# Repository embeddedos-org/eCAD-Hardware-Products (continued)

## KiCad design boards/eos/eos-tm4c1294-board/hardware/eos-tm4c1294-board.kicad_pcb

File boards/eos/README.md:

# EmbeddedOS development boards

Original boards designed by Kartikeydheer Srivastava, all rights reserved (see [Licence](#licence)).
Each board is written as a design file in [tools/eos_boards/boards](../../tools/eos_boards/boards). One command builds the
board's schematic, layout, routing, checks and fabrication outputs; see
[tools/eos_boards/README.md](../../tools/eos_boards/README.md).

| Board | What it is | Layers | ERC | DRC errors | Unconnected | Parity |
|---|---|---|---|---|---|---|
| [EoS Learn RP2350](eos-learn-rp2350) | RP2350A teaching board; Raspberry Pi's own core layout, reproduced to the nanometre | 4 | 0 | 0 | 0 | 0 |
| [EoS Sense Cape](eos-sense-cape) | Sensor cape for PocketBeagle; fit checked pin for pin against PocketBeagle's board file | 2 | 0 | 0 | 0 | 0 |
| [EoS Probe S3](eos-probe-s3) | ESP32-S3 SWD/JTAG + UART debug probe, 1.65–5.5 V targets | 2 | 0 | 0 | 0 | 0 |
| [EoS CM5 Base](eos-cm5-base) | Raspberry Pi CM5 carrier: USB-C power, Gigabit Ethernet, USB 2.0 host, microSD, 40-pin GPIO; connectors checked pad for pad against the CM5 | 4 | 0 | 0 | 0 | 0 |
| [EoS CM4 Base](eos-cm4-base) | Raspberry Pi CM4 carrier: USB-C power, one USB 2.0 port switched between USB-C (device) and USB-A (host), Gigabit Ethernet, microSD, 40-pin GPIO | 4 | 0 | 0 | 0 | 0 |
| [EoS Motion Wing](eos-motion-wing) | FeatherWing: ADXL343 accelerometer and ADT7410 temperature sensor on I2C, address and interrupt jumpers | 2 | 0 | 0 | 0 | 0 |
| [EoS ESP32 DevKit](eos-esp32-devkit) | ESP32-WROOM-32E board: USB-C, CP2102N USB-UART with auto-program, 3.3 V 1 A, DevKitC V4 header grid | 2 | 0 | 0 | 0 | 0 |
| [EoS ATmega328P Board](eos-atmega328p-board) | ATmega328P board that fits Uno R3 shields: USB-C, CH340C USB-UART with Ioff buffers, ICSP header | 2 | 0 | 0 | 0 | 0 |
| [EoS MSP430G2 Board](eos-msp430g2-board) | MSP430G2553 (DIP-20, socketed) board that takes 20-pin BoosterPacks; Spy-Bi-Wire header | 2 | 0 | 0 | 0 | 0 |
| [EoS TM4C123 Board](eos-tm4c123-board) | TM4C123GH6PM board that takes 40-pin BoosterPacks: USB device port, CP2102N USB-UART, SWD | 2 | 0 | 0 | 0 | 0 |
| [EoS KL25 Board](eos-kl25-board) | NXP KL25Z (MKL25Z128VLK4) board that fits Uno R3 shields: USB device port, accelerometer, SWD | 2 | 0 | 0 | 0 | 0 |
| [EoS STM32 64](eos-stm32-64) | STM32F411RE board in the 64-pin Nucleo format: morpho and Uno headers, 7-12 V buck, SWD | 2 | 0 | 0 | 0 | 0 |
| [EoS LPC55S69 Board](eos-lpc55s69-board) | NXP LPC55S69 (dual Cortex-M33) board that fits Uno R3 shields: two USB-C ports, power mux, SWD | 4 | 0 | 0 | 0 | 0 |
| [EoS KE16Z Board](eos-ke16z-board) | NXP KE16Z (MKE16Z64VLF4) board that fits Uno R3 shields: CP2102N USB-UART, CAN pins, SWD | 2 | 0 | 0 | 0 | 0 |
| [EoS RA2E1 Board](eos-ra2e1-board) | Renesas RA2E1 board that fits Uno R3 shields: two Pmod headers, CP2102N on the boot UART, SWD | 2 | 0 | 0 | 0 | 0 |
| [EoS F280049C Board](eos-f280049c-board) | TI TMS320F280049C (C2000) board with two 40-pin BoosterPack sites, four layers: CP2102N USB-UART, JTAG | 4 | 0 | 0 | 0 | 0 |
| [EoS RA4M2 Board](eos-ra4m2-board) | Renesas RA4M2 board that fits Uno R3 shields: SPI and I2C Pmod ports, 40-pin GPIO header, USB device, CP2102N, SWD | 2 | 0 | 0 | 0 | 0 |
| [EoS RL78G13 Board](eos-rl78g13-board) | Renesas RL78/G13 (R5F100LEAFB) stick board: two 30-pin headers 25.4 mm apart, USB-C serial port, TOOL0 debug | 2 | 0 | 0 | 0 | 0 |
| [EoS TM4C1294 Board](eos-tm4c1294-board) | TI TM4C1294NCPDT board with two 40-pin BoosterPack sites, a 98-hole breakout and 10/100 Ethernet, six layers: USB device port, CP2102N USB-UART, SWD/JTAG | 6 | 0 | 0 | 0 | 0 |
| [EoS Feather RP2040](eos-feather-rp2040) | RP2040 board in the Feather form factor: USB-C, LiPo charger, 16 MB QSPI flash, STEMMA QT, SWD | 4 | 0 | 0 | 0 | 0 |
| [EoS EPU Board](eos-epu-up5k) | iCE40UP5K FPGA board for EPU, EmbeddedOS's RISC-V SoC: USB-C with FT2232H (iceprog flash programming and UART), 16 MB flash, two Pmod ports, JTAG header | 4 | 0 | 0 | 0 | 0 |

Each board folder contains:

- the KiCad project;
- Gerbers and drill files;
- BOM and pick-and-place files;
- a STEP model;
- the schematic as a PDF;
- renders;
- `build-report.json`, which records the check counts.

The KiCad projects open in KiCad 10 or later; the boards are saved in KiCad 10's format.
The Gerbers, drill files, BOM, STEP and PDF need no KiCad at all.

None of these boards has been manufactured or tested on the bench. Each README says what was
checked and what was not.

## Licence

These boards are **not open source**, and they are **not** under the MIT licence that
covers this repository's own code. They are Copyright (c) 2026 Kartikeydheer Srivastava, all
rights reserved. Each board's `LICENSE.txt` has the full terms. In short:

- **Anyone** may view them, download or clone this repository, open the files to look at them
  and run its tests. Copying or changing the designs, making boards from them or selling them
  needs Kartikeydheer Srivastava's written permission, which may be given for a fee. To ask,
  write to kartikeydheer@gmail.com.
- **EmbeddedOS (EoS) Research Foundation** may, free of charge, publish them and its own
  changed versions for viewing, change them for its own projects, and make and lend boards for
  its own development, research, teaching and demonstrations. It may not sell boards or pass
  the designs on. Kartikeydheer Srivastava can withdraw this permission with 30 days' notice
  by email or letter.
- **Third-party material** keeps its own licence: Raspberry Pi's RP2350A core layout (MIT) on
  EoS Learn RP2350, and footprints, symbols and 3D models from KiCad's libraries. Each board's
  `LICENSE.txt` lists what it uses.

What the licence covers:

- every board folder here, except the generic libraries copied into a board's
  `hardware/symbols/` and `hardware/footprints/EoS_Packages.pretty`, which are MIT like the
  generator that writes them;
- in `tools/eos_boards`: the boards' design files `boards/eos_*.py`, `boards/owner.py`, the
  licence terms `boards/licence_terms.txt`, and the footprint library drawn for the module
  carriers, `footprints/EoS_Connectors.pretty`.

The rest of `tools/eos_boards` (the generator, the reference extractors, `symbols/` and
`footprints/generate.py` with the `EoS_Packages.pretty` it writes) and its tests stay under the
repository's MIT licence.

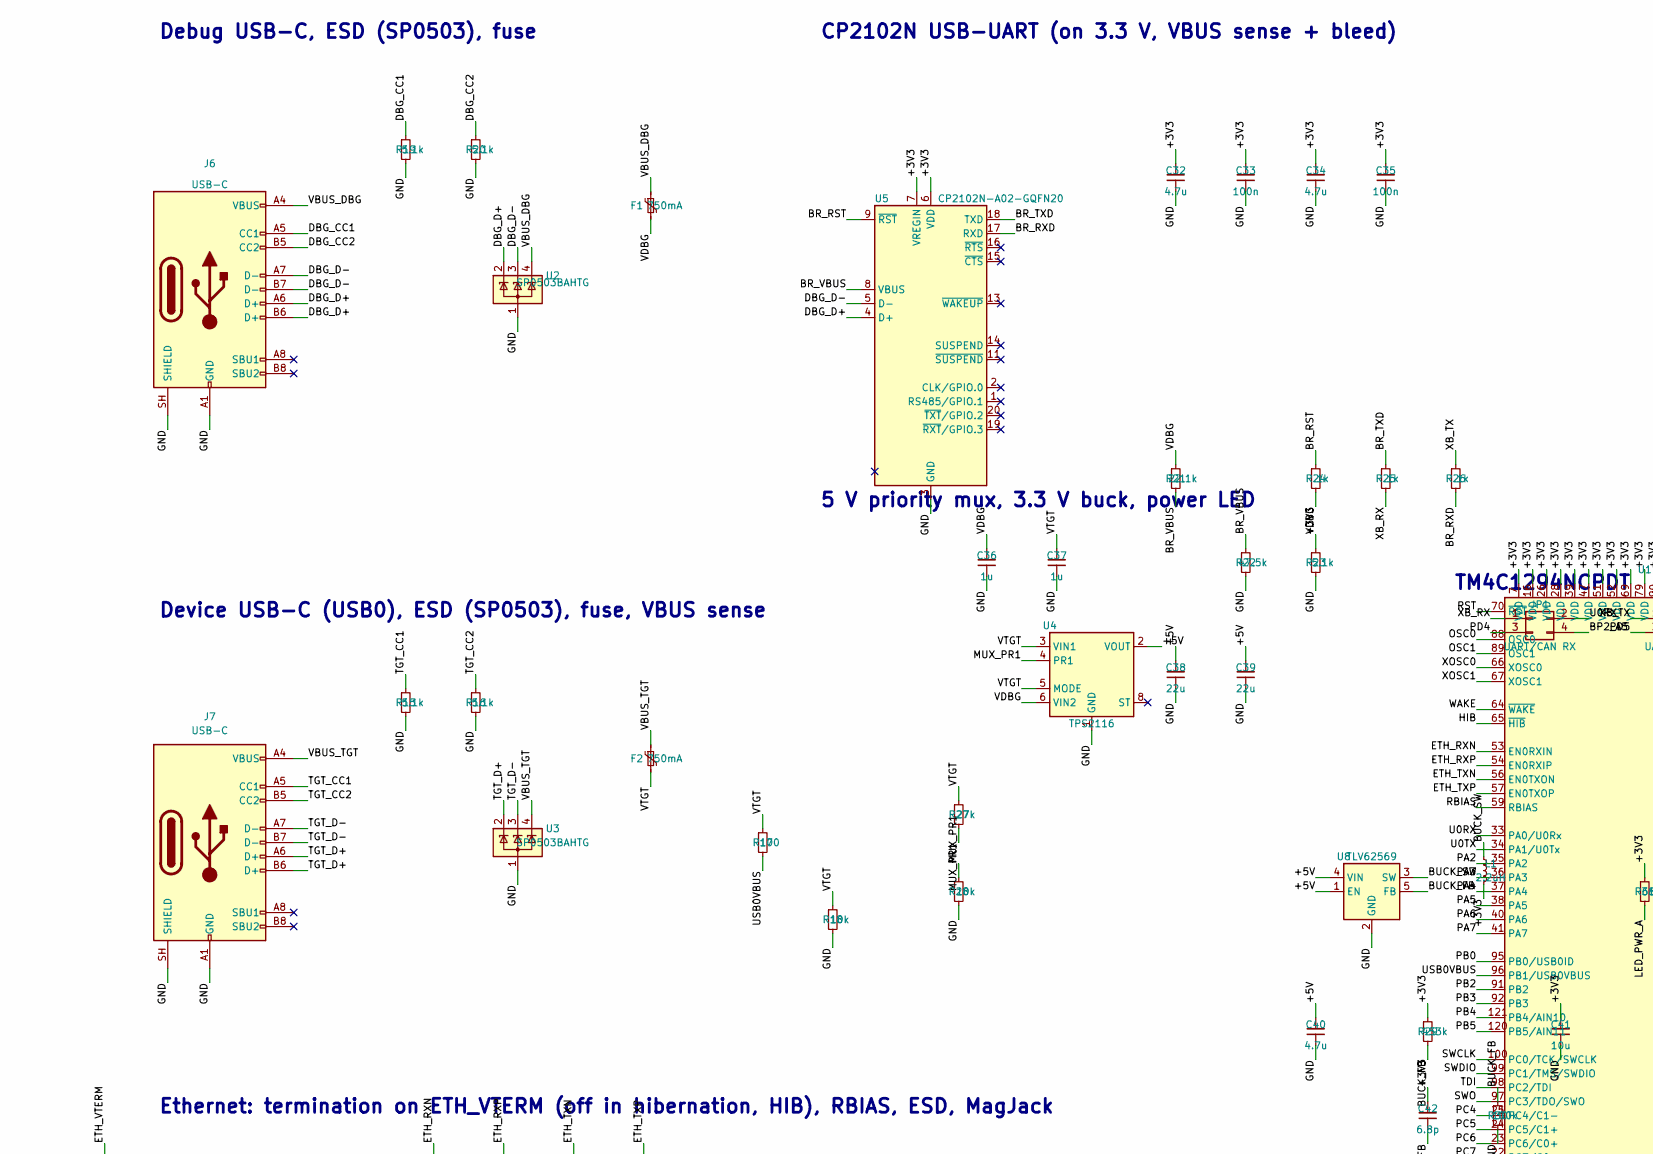
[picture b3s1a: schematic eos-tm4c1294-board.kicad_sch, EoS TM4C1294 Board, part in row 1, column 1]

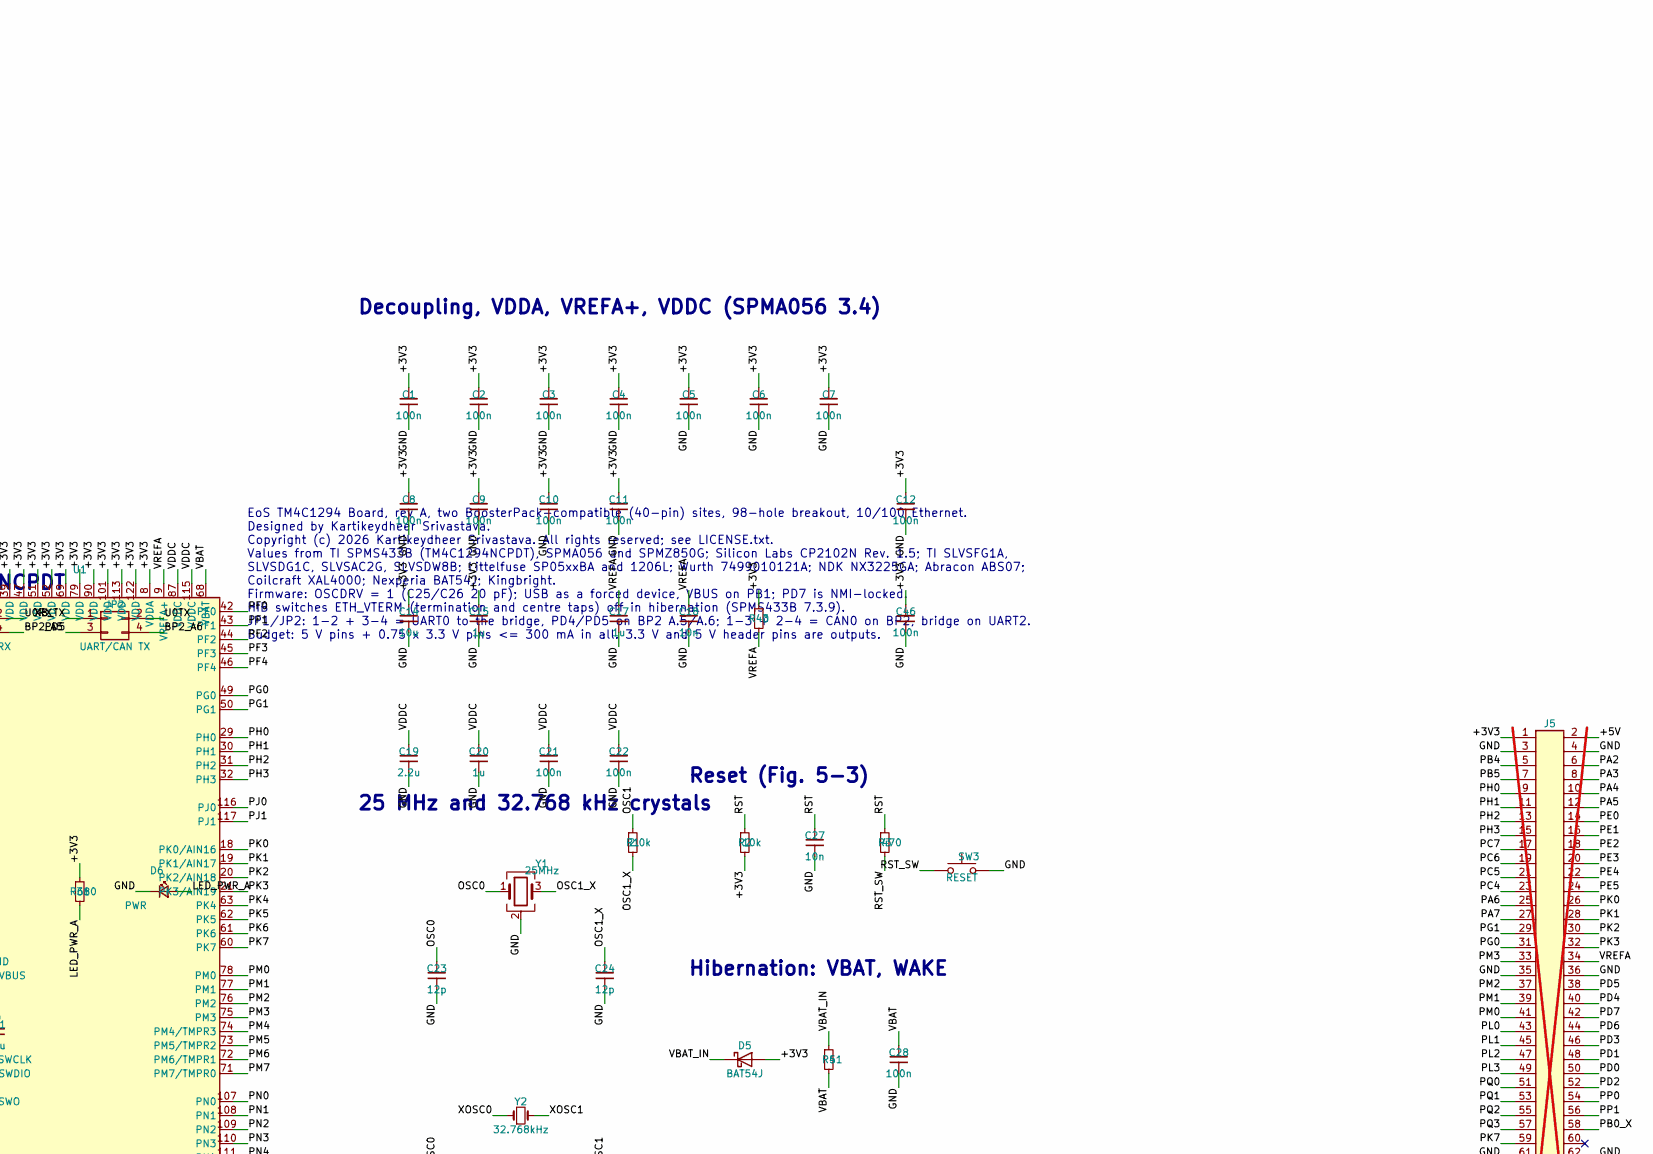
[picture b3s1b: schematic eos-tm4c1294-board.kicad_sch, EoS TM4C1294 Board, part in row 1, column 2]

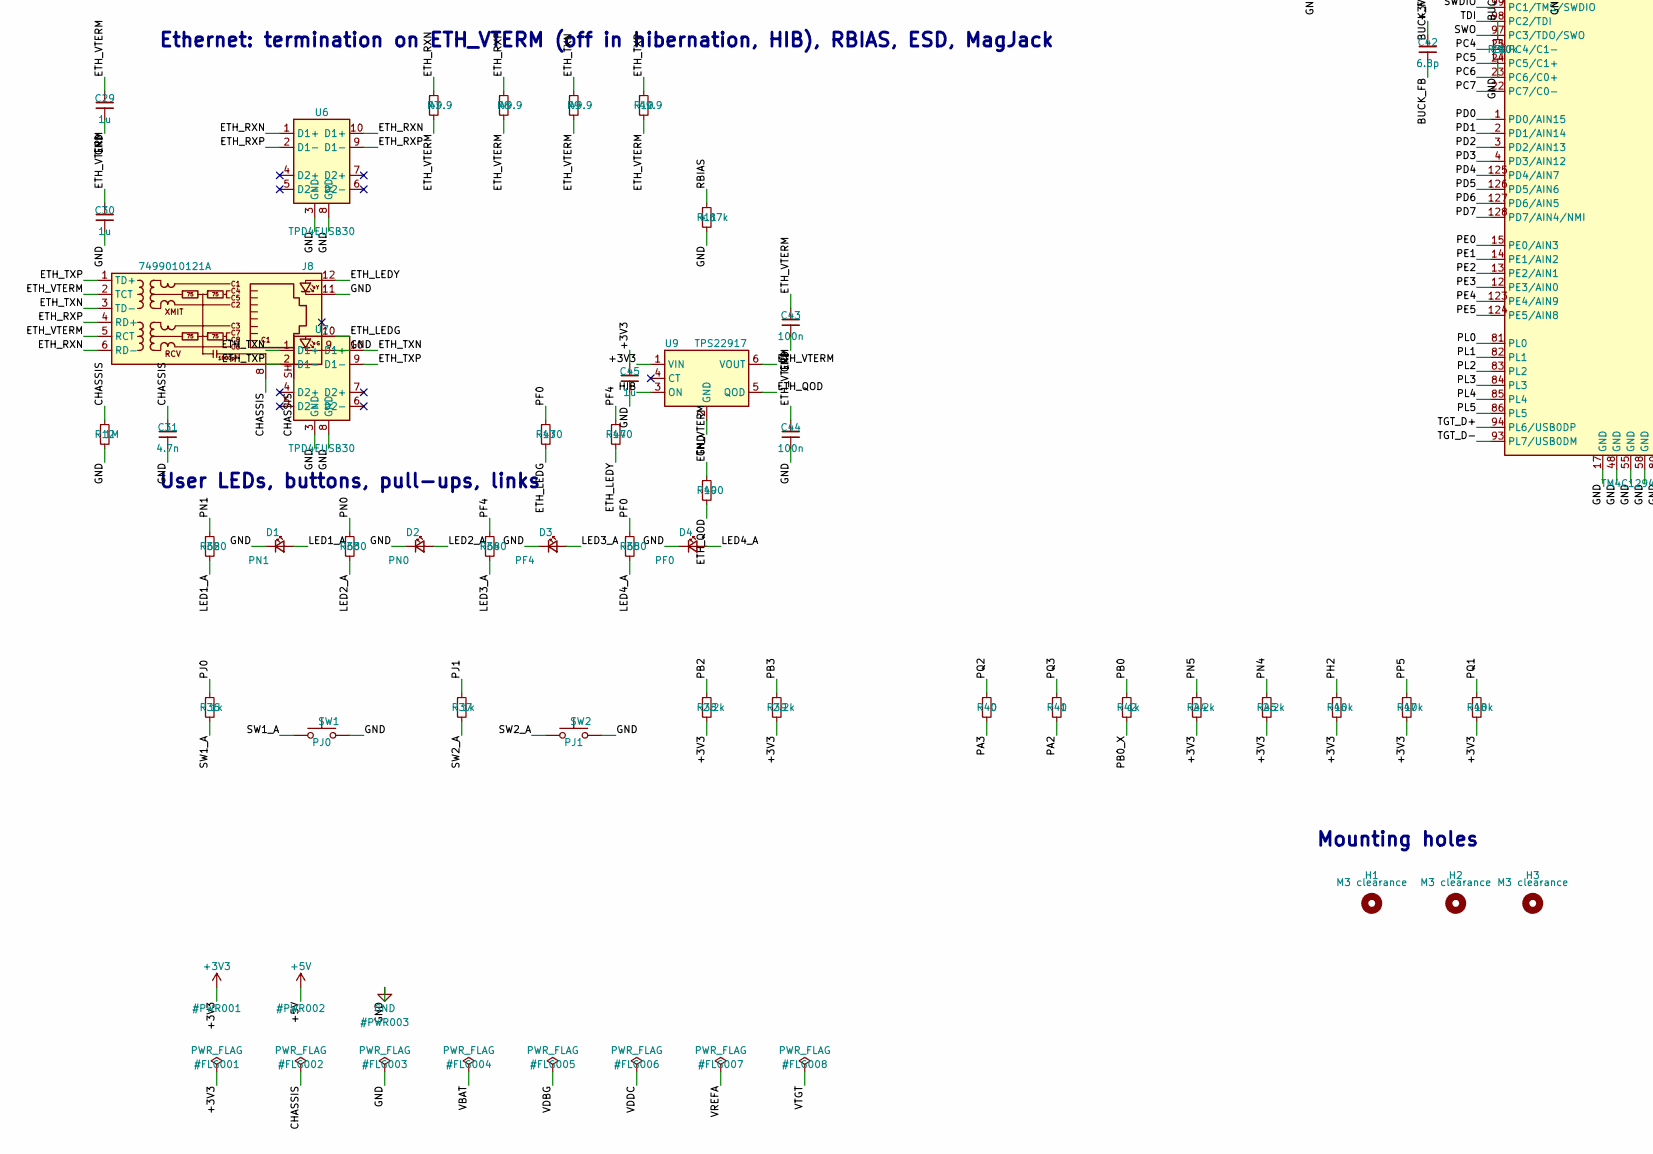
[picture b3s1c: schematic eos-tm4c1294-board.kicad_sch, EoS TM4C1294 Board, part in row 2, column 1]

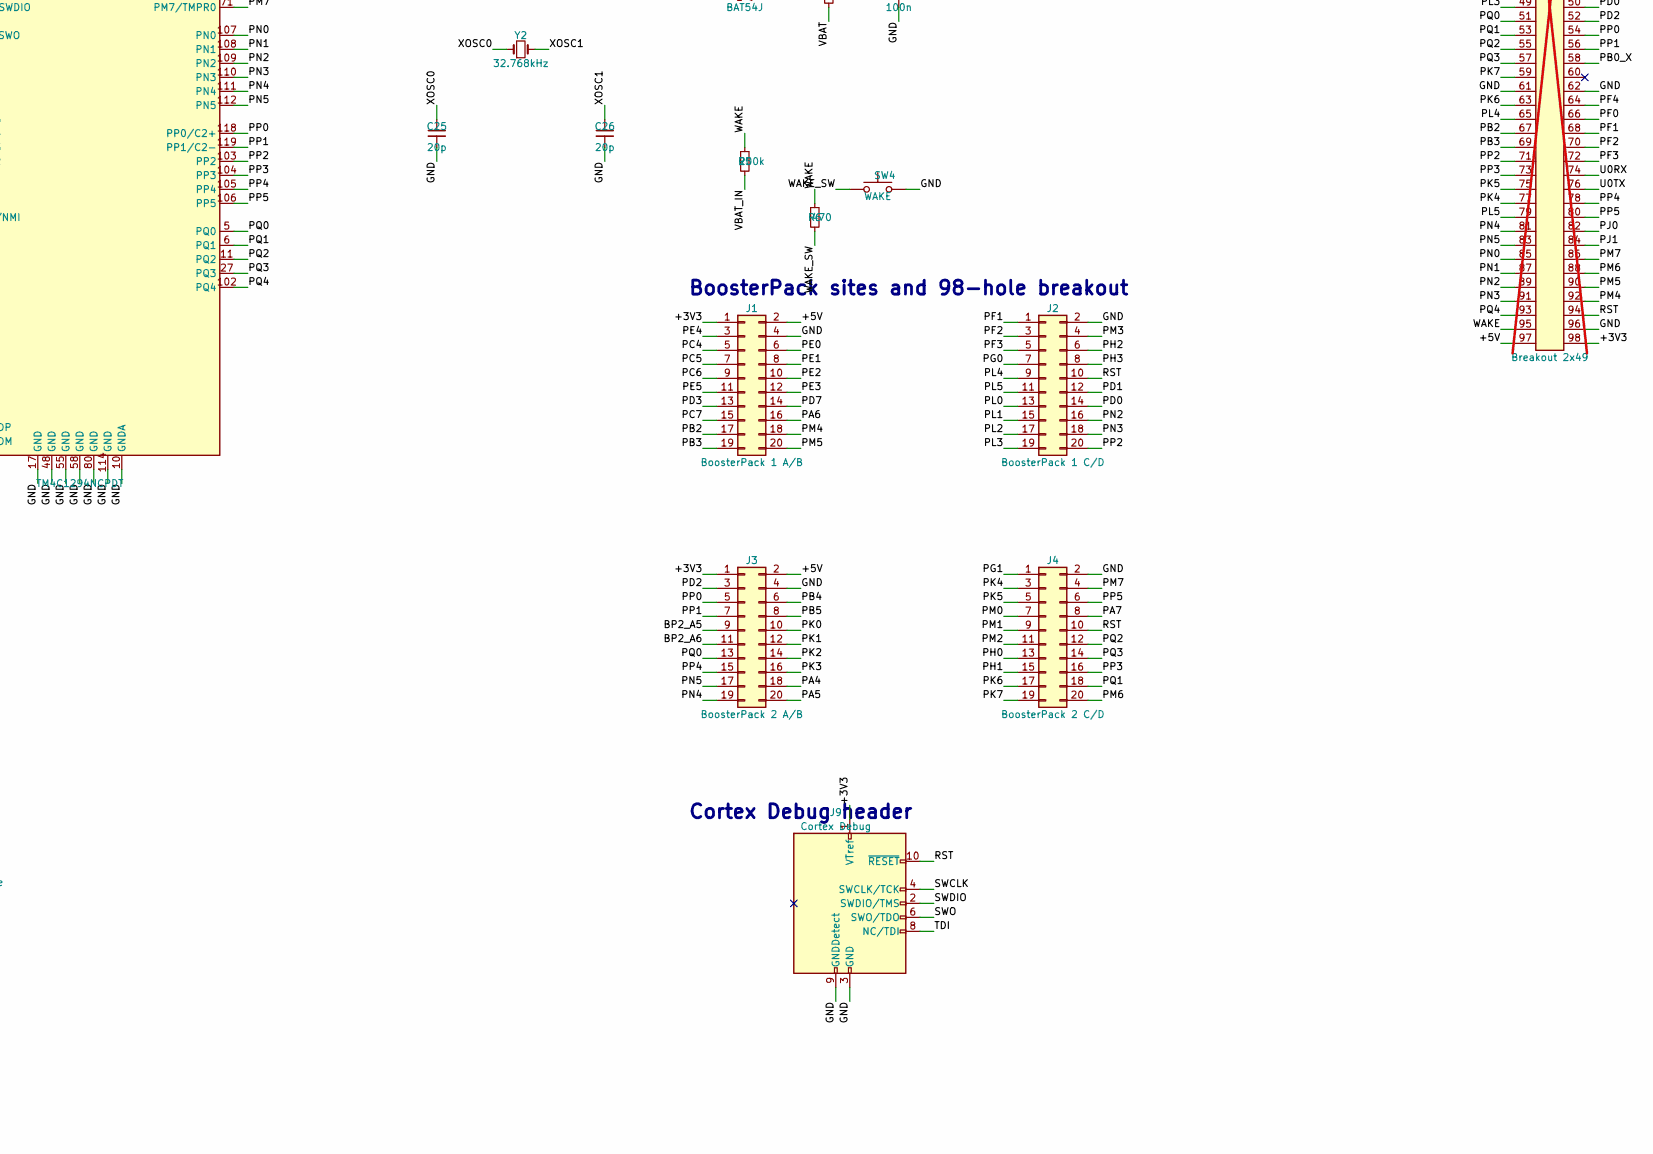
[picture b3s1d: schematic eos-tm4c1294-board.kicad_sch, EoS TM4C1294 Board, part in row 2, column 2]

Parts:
C1, C2, C3, C4, C5, C6, C7, C8, C9, C10, C11, C12, C21, C22, C28, C33, C35, C43, C44, C46: 100n; C_0402_1005Metric; MPN GRM155R71C104KA88D
C14: 10u; C_0805_2012Metric; MPN GRM21BR61C106KE15L
C15, C17, C20, C29, C30, C36, C37, C45: 1u; C_0603_1608Metric; MPN GCM188R71C105KA64D
C18, C27: 10n; C_0402_1005Metric; MPN GRM155R71H103KA88D
C19: 2.2u; C_0603_1608Metric; MPN GRM188R71A225KE15D
C23, C24: 12p; C_0402_1005Metric; MPN GRM1555C1H120JA01D
C25, C26: 20p; C_0402_1005Metric; MPN GCM1555C1H200JA16D
C31: 4.7n; C_1812_4532Metric; MPN C1812C472KGRACTU
C32, C34: 4.7u; C_0603_1608Metric; MPN GRM188R61C475KE11D
C38, C39: 22u; C_1206_3216Metric; MPN GRM31CR71A226KE15L
C40: 4.7u; C_0805_2012Metric; MPN GRM21BR71A475KE51L
C41: 10u; C_0805_2012Metric; MPN GRM21BR71A106KA73L
C42: 6.8p; C_0402_1005Metric; MPN GRM1555C1H6R8CA01D
D1: PN1; LED_0603_1608Metric; MPN APTD1608LCGCK
D2: PN0; LED_0603_1608Metric; MPN APTD1608LCGCK
D3: PF4; LED_0603_1608Metric; MPN APTD1608LCGCK
D4: PF0; LED_0603_1608Metric; MPN APTD1608LCGCK
D5: BAT54J; D_SOD-323F; MPN BAT54J
D6: PWR; LED_0603_1608Metric; MPN APTD1608LCGCK
F1, F2: 750mA; Fuse_1206_3216Metric; MPN 1206L075THYR
H1, H2, H3: M3 clearance; MountingHole_3.2mm_M3
J1: BoosterPack 1 A/B; PinHeader_2x10_P2.54mm_Vertical; MPN SSW-110-23-F-D
J2: BoosterPack 1 C/D; PinHeader_2x10_P2.54mm_Vertical; MPN SSW-110-23-F-D
J3: BoosterPack 2 A/B; PinHeader_2x10_P2.54mm_Vertical; MPN SSW-110-23-F-D
J4: BoosterPack 2 C/D; PinHeader_2x10_P2.54mm_Vertical; MPN SSW-110-23-F-D
J5: Breakout 2x49; PinHeader_2x49_P2.54mm_Vertical; not fitted
J6, J7: USB-C; USB_C_Receptacle_HRO_TYPE-C-31-M-12; MPN TYPE-C-31-M-12
J8: 7499010121A; RJ45_Wuerth_7499010121A_Horizontal; MPN 7499010121A
J9: Cortex Debug; PinHeader_2x05_P1.27mm_Vertical_SMD; MPN FTSH-105-01-L-DV-K
JP1: UART/CAN RX; PinHeader_2x02_P2.54mm_Vertical; MPN TSW-102-07-G-D
JP2: UART/CAN TX; PinHeader_2x02_P2.54mm_Vertical; MPN TSW-102-07-G-D
L1: 2.2uH; L_Coilcraft_XAL4020-XXX; MPN XAL4020-222MEC
R1: 2.0k; R_0402_1005Metric
R2, R18, R28, R46, R47, R48: 10k; R_0402_1005Metric
R3, R6, R13, R14: 470; R_0402_1005Metric
R4: 51; R_0402_1005Metric
R5: 200k; R_0402_1005Metric
R7, R8, R9, R10: 49.9; R_0402_1005Metric
R11: 4.87k; R_0402_1005Metric
R12: 1M; R_1206_3216Metric
R15, R16, R19, R20, R23: 5.1k; R_0402_1005Metric
R17, R49: 100; R_0402_1005Metric
R21: 22.1k; R_0402_1005Metric
R22: 47.5k; R_0402_1005Metric
R24, R25, R26, R36, R37, R42: 1k; R_0402_1005Metric
R27: 27k; R_0402_1005Metric
R29: 453k; R_0402_1005Metric
R30: 100k; R_0402_1005Metric
R31, R32, R33, R34, R35: 680; R_0402_1005Metric
R38, R39, R44, R45: 2.2k; R_0402_1005Metric
R40, R41, R43: 0; R_0402_1005Metric
SW1: PJ0; SW_Push_1P1T_NO_CK_KMR2; MPN KMR221G LFS
SW2: PJ1; SW_Push_1P1T_NO_CK_KMR2; MPN KMR221G LFS
SW3: RESET; SW_Push_1P1T_NO_CK_KMR2; MPN KMR221G LFS
SW4: WAKE; SW_Push_1P1T_NO_CK_KMR2; MPN KMR221G LFS
U1: TM4C1294NCPDT; TQFP-128_14x14mm_P0.4mm; MPN TM4C1294NCPDTI3
U2, U3: SP0503BAHTG; SOT-143; MPN SP0503BAHTG
U4: TPS2116; SOT-583-8; MPN TPS2116DRLR
U5: CP2102N-A02-GQFN20; SiliconLabs_QFN-20-1EP_3x3mm_P0.5mm_EP1.8x1.8mm; MPN CP2102N-A02-GQFN20R
U6, U7: TPD4EUSB30; USON-10_2.5x1.0mm_P0.5mm; MPN TPD4EUSB30DQAR
U8: TLV62569; SOT-23-5; MPN TLV62569DBVR
U9: TPS22917; SOT-23-6; MPN TPS22917DBVR
Y1: 25MHz; Crystal_SMD_3225-4Pin_3.2x2.5mm; MPN NX3225GA-25.000M-STD-CRG-2
Y2: 32.768kHz; Crystal_SMD_3215-2Pin_3.2x1.5mm; MPN ABS07-32.768KHZ-T

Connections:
+3V3: C1.1, C2.1, C3.1, C4.1, C5.1, C6.1, C7.1, C8.1, C9.1, C10.1, C11.1, C12.1, C14.1, C15.1, C32.1, C33.1, C34.1, C35.1, C41.1, C42.1, C45.1, C46.1, D5.2 (A), J1.1, J3.1, J5.1, J5.98, J9.1 (VTref), L1.2, R2.2, R24.2, R29.1, R31.1, R38.2, R39.2, R43.1, R44.2, R45.2, R46.2, R47.2, R48.2, U1.7 (VDD), U1.8 (VDDA), U1.16 (VDD), U1.26 (VDD), U1.28 (VDD), U1.39 (VDD), U1.47 (VDD), U1.51 (VDD), U1.52 (VDD), U1.69 (VDD), U1.79 (VDD), U1.90 (VDD), U1.101 (VDD), U1.113 (VDD), U1.122 (VDD), U5.6 (VDD), U5.7 (VREGIN), U9.1 (VIN)
+5V: C38.1, C39.1, C40.1, J1.2, J3.2, J5.2, J5.97, U4.2 (VOUT), U4.7 (VOUT), U8.1 (EN), U8.4 (VIN)
/BP2_A5: J3.9, JP1.4
/BP2_A6: J3.11, JP2.4
/BR_RST: R24.1, U5.9 (~RST)
/BR_RXD: R26.2, U5.17 (RXD)
/BR_TXD: R25.1, U5.18 (TXD)
/BR_VBUS: R21.2, R22.1, U5.8 (VBUS)
/BUCK_FB: C42.2, R29.2, R30.1, U8.5 (FB)
/BUCK_SW: L1.1, U8.3 (SW)
/CHASSIS: C31.1, J8.8, J8.SH, R12.1
/DBG_CC1: J6.A5 (CC1), R19.1
/DBG_CC2: J6.B5 (CC2), R20.1
/DBG_D+: J6.A6 (D+), J6.B6 (D+), U2.2 (K), U5.4 (D+)
/DBG_D-: J6.A7 (D-), J6.B7 (D-), U2.3 (K), U5.5 (D-)
/ETH_LEDG: J8.10, R13.2
/ETH_LEDY: J8.12, R14.2
/ETH_QOD: R49.2, U9.5 (QOD)
/ETH_RXN: J8.6 (RD-), R7.1, U1.53 (EN0RXIN), U6.1 (D1+), U6.10 (D1+)
/ETH_RXP: J8.4 (RD+), R8.1, U1.54 (EN0RXIP), U6.2 (D1-), U6.9 (D1-)
/ETH_TXN: J8.3 (TD-), R9.1, U1.56 (EN0TXON), U7.1 (D1+), U7.10 (D1+)
/ETH_TXP: J8.1 (TD+), R10.1, U1.57 (EN0TXOP), U7.2 (D1-), U7.9 (D1-)
/ETH_VTERM: C29.1, C30.1, C43.1, C44.1, J8.2 (TCT), J8.5 (RCT), R7.2, R8.2, R9.2, R10.2, R49.1, U9.6 (VOUT)
/HIB: U1.65 (~HIB), U9.3 (ON)
/LED1_A: D1.2 (A), R32.2
/LED2_A: D2.2 (A), R33.2
/LED3_A: D3.2 (A), R34.2
/LED4_A: D4.2 (A), R35.2
/LED_PWR_A: D6.2 (A), R31.2
/MUX_PR1: R27.2, R28.1, U4.4 (PR1)
/OSC0: C23.1, U1.88 (OSC0), Y1.1
/OSC1: R1.1, U1.89 (OSC1)
/OSC1_X: C24.1, R1.2, Y1.3
/PA2: J5.6, R41.2, U1.35 (PA2)
/PA3: J5.8, R40.2, U1.36 (PA3)
/PA4: J3.18, J5.10, U1.37 (PA4)
/PA5: J3.20, J5.12, U1.38 (PA5)
/PA6: J1.16, J5.25, U1.40 (PA6)
/PA7: J4.8, J5.27, U1.41 (PA7)
/PB0: R42.1, U1.95 (PB0/USB0ID)
/PB0_X: J5.58, R42.2
/PB2: J1.17, J5.67, R38.1, U1.91 (PB2)
/PB3: J1.19, J5.69, R39.1, U1.92 (PB3)
/PB4: J3.6, J5.5, U1.121 (PB4/AIN10)
/PB5: J3.8, J5.7, U1.120 (PB5/AIN11)
/PC4: J1.5, J5.23, U1.25 (PC4/C1-)
/PC5: J1.7, J5.21, U1.24 (PC5/C1+)
/PC6: J1.9, J5.19, U1.23 (PC6/C0+)
/PC7: J1.15, J5.17, U1.22 (PC7/C0-)
/PD0: J2.14, J5.50, U1.1 (PD0/AIN15)
/PD1: J2.12, J5.48, U1.2 (PD1/AIN14)
/PD2: J3.3, J5.52, U1.3 (PD2/AIN13)
/PD3: J1.13, J5.46, U1.4 (PD3/AIN12)
/PD4: J5.40, JP1.3, U1.125 (PD4/AIN7)
/PD5: J5.38, JP2.3, U1.126 (PD5/AIN6)
/PD6: J5.44, U1.127 (PD6/AIN5)
/PD7: J1.14, J5.42, U1.128 (PD7/AIN4/NMI)
/PE0: J1.6, J5.14, U1.15 (PE0/AIN3)
/PE1: J1.8, J5.16, U1.14 (PE1/AIN2)
/PE2: J1.10, J5.18, U1.13 (PE2/AIN1)
/PE3: J1.12, J5.20, U1.12 (PE3/AIN0)
/PE4: J1.3, J5.22, U1.123 (PE4/AIN9)
/PE5: J1.11, J5.24, U1.124 (PE5/AIN8)
/PF0: J5.66, R13.1, R35.1, U1.42 (PF0)
/PF1: J2.1, J5.68, U1.43 (PF1)
/PF2: J2.3, J5.70, U1.44 (PF2)
/PF3: J2.5, J5.72, U1.45 (PF3)
/PF4: J5.64, R14.1, R34.1, U1.46 (PF4)
/PG0: J2.7, J5.31, U1.49 (PG0)
/PG1: J4.1, J5.29, U1.50 (PG1)
/PH0: J4.13, J5.9, U1.29 (PH0)
/PH1: J4.15, J5.11, U1.30 (PH1)
/PH2: J2.6, J5.13, R46.1, U1.31 (PH2)
/PH3: J2.8, J5.15, U1.32 (PH3)
/PJ0: J5.82, R36.1, U1.116 (PJ0)
/PJ1: J5.84, R37.1, U1.117 (PJ1)
/PK0: J3.10, J5.26, U1.18 (PK0/AIN16)
/PK1: J3.12, J5.28, U1.19 (PK1/AIN17)
/PK2: J3.14, J5.30, U1.20 (PK2/AIN18)
/PK3: J3.16, J5.32, U1.21 (PK3/AIN19)
/PK4: J4.3, J5.77, U1.63 (PK4)
/PK5: J4.5, J5.75, U1.62 (PK5)
/PK6: J4.17, J5.63, U1.61 (PK6)
/PK7: J4.19, J5.59, U1.60 (PK7)
/PL0: J2.13, J5.43, U1.81 (PL0)
/PL1: J2.15, J5.45, U1.82 (PL1)
/PL2: J2.17, J5.47, U1.83 (PL2)
/PL3: J2.19, J5.49, U1.84 (PL3)
/PL4: J2.9, J5.65, U1.85 (PL4)
/PL5: J2.11, J5.79, U1.86 (PL5)
/PM0: J4.7, J5.41, U1.78 (PM0)
/PM1: J4.9, J5.39, U1.77 (PM1)
/PM2: J4.11, J5.37, U1.76 (PM2)
/PM3: J2.4, J5.33, U1.75 (PM3)
/PM4: J1.18, J5.92, U1.74 (PM4/TMPR3)
/PM5: J1.20, J5.90, U1.73 (PM5/TMPR2)
/PM6: J4.20, J5.88, U1.72 (PM6/TMPR1)
/PM7: J4.4, J5.86, U1.71 (PM7/TMPR0)
/PN0: J5.85, R33.1, U1.107 (PN0)
/PN1: J5.87, R32.1, U1.108 (PN1)
/PN2: J2.16, J5.89, U1.109 (PN2)
/PN3: J2.18, J5.91, U1.110 (PN3)
/PN4: J3.19, J5.81, R45.1, U1.111 (PN4)
/PN5: J3.17, J5.83, R44.1, U1.112 (PN5)
/PP0: J3.5, J5.54, U1.118 (PP0/C2+)
/PP1: J3.7, J5.56, U1.119 (PP1/C2-)
/PP2: J2.20, J5.71, U1.103 (PP2)
/PP3: J4.16, J5.73, U1.104 (PP3)
/PP4: J3.15, J5.78, U1.105 (PP4)
/PP5: J4.6, J5.80, R47.1, U1.106 (PP5)
/PQ0: J3.13, J5.51, U1.5 (PQ0)
/PQ1: J4.18, J5.53, R48.1, U1.6 (PQ1)
/PQ2: J4.12, J5.55, R40.1, U1.11 (PQ2)
/PQ3: J4.14, J5.57, R41.1, U1.27 (PQ3)
/PQ4: J5.93, U1.102 (PQ4)
/RBIAS: R11.1, U1.59 (RBIAS)
/RST: C27.1, J2.10, J4.10, J5.94, J9.10 (~RESET), R2.1, R3.1, U1.70 (~RST)
/RST_SW: R3.2, SW3.1
/SW1_A: R36.2, SW1.1
/SW2_A: R37.2, SW2.1
/SWCLK: J9.4 (SWCLK/TCK), U1.100 (PC0/TCK/SWCLK)
/SWDIO: J9.2 (SWDIO/TMS), U1.99 (PC1/TMS/SWDIO)
/SWO: J9.6 (SWO/TDO), U1.97 (PC3/TDO/SWO)
/TDI: J9.8 (NC/TDI), U1.98 (PC2/TDI)
/TGT_CC1: J7.A5 (CC1), R15.1
/TGT_CC2: J7.B5 (CC2), R16.1
/TGT_D+: J7.A6 (D+), J7.B6 (D+), U1.94 (PL6/USB0DP), U3.2 (K)
/TGT_D-: J7.A7 (D-), J7.B7 (D-), U1.93 (PL7/USB0DM), U3.3 (K)
/U0RX: J5.74, JP1.2, U1.33 (PA0/U0Rx)
/U0TX: J5.76, JP2.2, U1.34 (PA1/U0Tx)
/USB0VBUS: R17.2, U1.96 (PB1/USB0VBUS)
/VBAT: C28.1, R4.2, U1.68 (VBAT)
/VBAT_IN: D5.1 (K), R4.1, R5.2
/VBUS_DBG: F1.1, J6.A4 (VBUS), J6.A9 (VBUS), J6.B4 (VBUS), J6.B9 (VBUS), U2.4 (K)
/VBUS_TGT: F2.1, J7.A4 (VBUS), J7.A9 (VBUS), J7.B4 (VBUS), J7.B9 (VBUS), U3.4 (K)
/VDBG: C36.1, F1.2, R21.1, R23.1, U4.6 (VIN2)
/VDDC: C19.1, C20.1, C21.1, C22.1, U1.87 (VDDC), U1.115 (VDDC)
/VREFA: C17.1, C18.1, J5.34, R43.2, U1.9 (VREFA+)
/VTGT: C37.1, F2.2, R17.1, R18.1, R27.1, U4.3 (VIN1), U4.5 (MODE)
/WAKE: J5.95, R5.1, R6.1, U1.64 (~WAKE)
/WAKE_SW: R6.2, SW4.1
/XB_RX: JP1.1, R25.2
/XB_TX: JP2.1, R26.1
/XOSC0: C25.1, U1.66 (XOSC0), Y2.1
/XOSC1: C26.1, U1.67 (XOSC1), Y2.2
GND: C1.2, C2.2, C3.2, C4.2, C5.2, C6.2, C7.2, C8.2, C9.2, C10.2, C11.2, C12.2, C14.2, C15.2, C17.2, C18.2, C19.2, C20.2, C21.2, C22.2, C23.2, C24.2, C25.2, C26.2, C27.2, C28.2, C29.2, C30.2, C31.2, C32.2, C33.2, C34.2, C35.2, C36.2, C37.2, C38.2, C39.2, C40.2, C41.2, C43.2, C44.2, C45.2, C46.2, D1.1 (K), D2.1 (K), D3.1 (K), D4.1 (K), D6.1 (K), J1.4, J2.2, J3.4, J4.2, J5.3, J5.4, J5.35, J5.36, J5.61, J5.62, J5.96, J6.A1 (GND), J6.A12 (GND), J6.B1 (GND), J6.B12 (GND), J6.SH (SHIELD), J7.A1 (GND), J7.A12 (GND), J7.B1 (GND), J7.B12 (GND), J7.SH (SHIELD), J8.9, J8.11, J9.3 (GND), J9.5 (GND), J9.9 (GNDDetect), R11.2, R12.2, R15.2, R16.2, R18.2, R19.2, R20.2, R22.2, R23.2, R28.2, R30.2, SW1.2, SW2.2, SW3.2, SW4.2, U1.10 (GNDA), U1.17 (GND), U1.48 (GND), U1.55 (GND), U1.58 (GND), U1.80 (GND), U1.114 (GND), U2.1 (A), U3.1 (A), U4.1 (GND), U5.3 (GND), U5.12 (GND), U5.21 (GND), U6.3 (GND), U6.8 (GND), U7.3 (GND), U7.8 (GND), U8.2 (GND), U9.2 (GND), Y1.2 (G), Y1.4 (G)

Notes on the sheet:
Debug USB-C, ESD (SP0503), fuse
CP2102N USB-UART (on 3.3 V, VBUS sense + bleed)
Device USB-C (USB0), ESD (SP0503), fuse, VBUS sense
5 V priority mux, 3.3 V buck, power LED
TM4C1294NCPDT
Decoupling, VDDA, VREFA+, VDDC (SPMA056 3.4)
25 MHz and 32.768 kHz crystals
Reset (Fig. 5-3)
Hibernation: VBAT, WAKE
Ethernet: termination on ETH_VTERM (off in hibernation, HIB), RBIAS, ESD, MagJack
BoosterPack sites and 98-hole breakout
Cortex Debug header
User LEDs, buttons, pull-ups, links
Mounting holes
EoS TM4C1294 Board, rev A, two BoosterPack-compatible (40-pin) sites, 98-hole breakout, 10/100 Ethernet. Designed by Kartikeydheer Srivastava. Copyright (c) 2026 Kartikeydheer Srivastava. All rights reserved; see LICENSE.txt. Values from TI SPMS433B (TM4C1294NCPDT), SPMA056 and SPMZ850G; Silicon La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

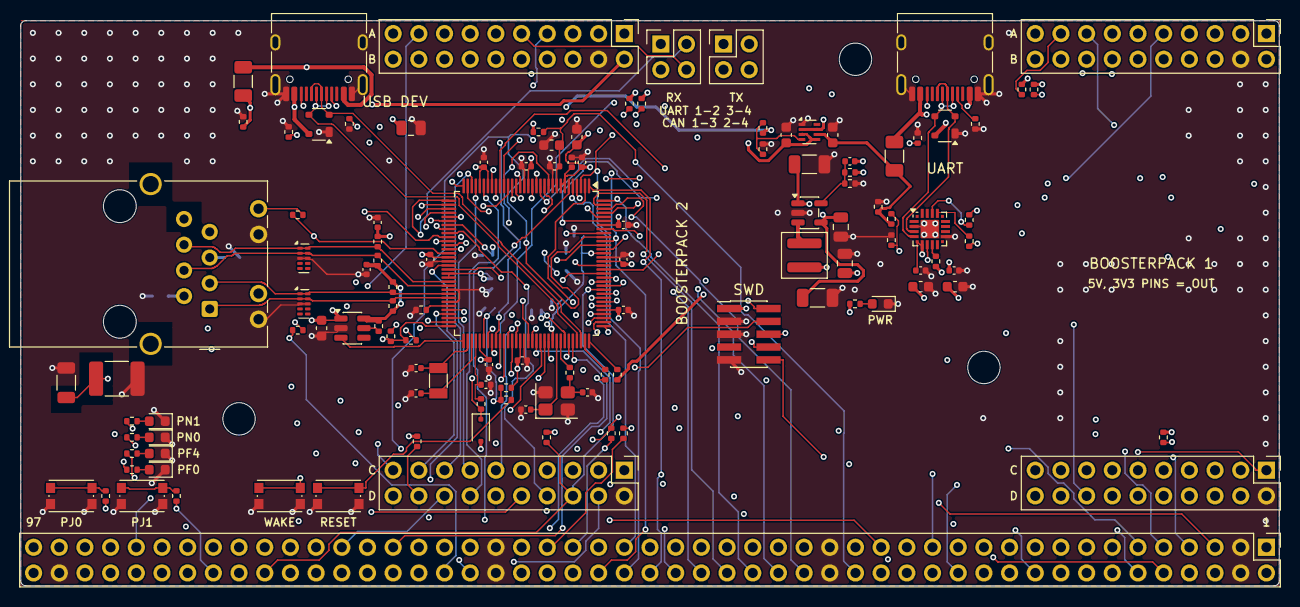
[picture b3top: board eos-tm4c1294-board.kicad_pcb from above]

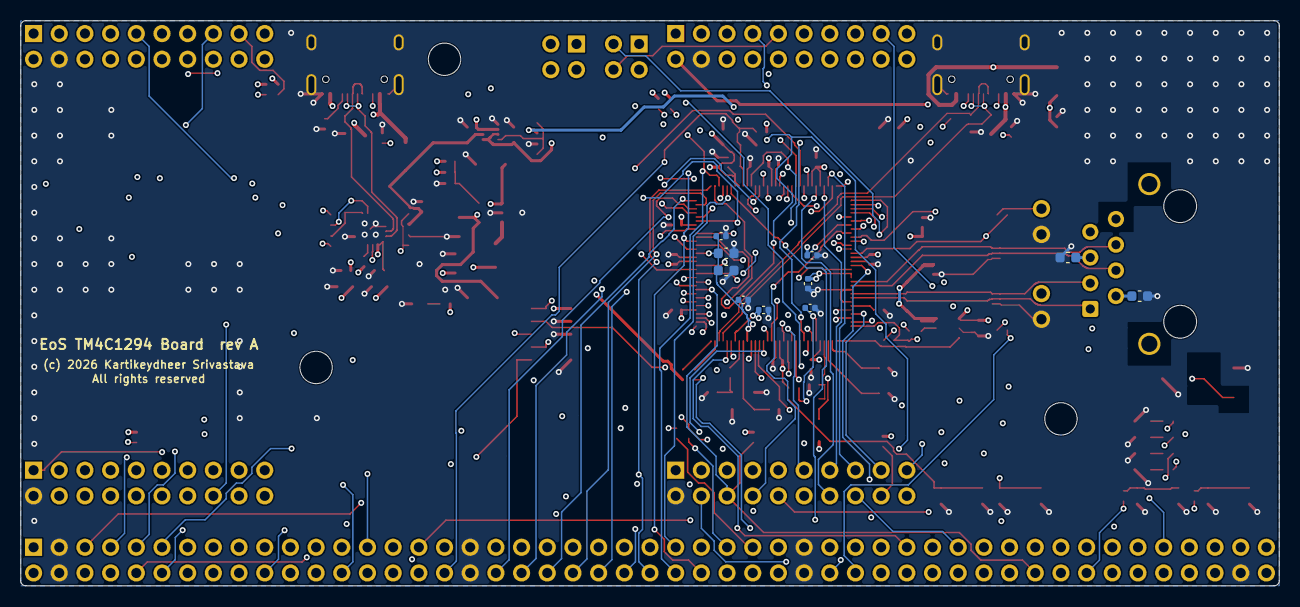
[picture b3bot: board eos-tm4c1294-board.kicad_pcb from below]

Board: 6 copper layers, 124.5 x 55.9 mm, 131 parts (10 on the bottom side), 146 nets.

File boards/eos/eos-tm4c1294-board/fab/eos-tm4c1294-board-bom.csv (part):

"Refs","Value","Footprint","Manufacturer","MPN","Description","Qty","DNP"
"C1-C12,C21,C22,C28,C33,C35,C43,C44,C46","100n","Capacitor_SMD:C_0402_1005Metric","Murata","GRM155R71C104KA88D","Capacitor 100 nF X7R 16 V 0402, CBAT at VBAT pin 68: 5.1 us with RBAT, under 0.7 V/us (TI SPMS433B Figure 7-2, Table 27-29; errata ELEC#02),Capacitor 100 nF X7R 16 V 0402, CP2102N VDD, at the pin (Silicon Labs CP2102N data sheet Rev. 1.5 Figure 2.3),Capacitor 100 nF X7R 16 V 0402, CP2102N VREGIN, at the pin (Silicon Labs CP2102N data sheet Rev. 1.5 Figure 2.3),Capacitor 100 nF X7R 16 V 0402, VDD pin 101, joined to the pin before routing (TI SPMA056 3.4.3),Capacitor 100 nF X7R 16 V 0402, VDD pin 113, joined to the pin before routing (TI SPMA056 3.4.3),Capacitor 100 nF X7R 16 V 0402, VDD pin 122, joined to the pin before routing (TI SPMA056 3.4.3),Capacitor 100 nF X7R 16 V 0402, VDD pin 16, joined to the pin before routing (TI SPMA056 3.4.3),Capacitor 100 nF X7R 16 V 0402, VDD pin 26/28, joined to the pin before routing (TI SPMA056 3.4.3),Capacitor 100 nF X7R 16 V 0402, VDD pin 39, joined to the pin before routing (TI SPMA056 3.4.3; on the bottom side under the chip, reached through a via inside the pad ring (Table 7)),Capacitor 100 nF X7R 16 V 0402, VDD pin 47, joined to the pin before routing (TI SPMA056 3.4.3),Capacitor 100 nF X7R 16 V 0402, VDD pin 51/52, joined to the pin before routing (TI SPMA056 3.4.3; on the bottom side under the chip, through a via inside the pad ring (Table 7); its ground pad also takes GND pins 55 and 58),Capacitor 100 nF X7R 16 V 0402, VDD pin 69, joined to the pin before routing (TI SPMA056 3.4.3),Capacitor 100 nF X7R 16 V 0402, VDD pin 7, joined to the pin before routing (TI SPMA056 3.4.3),Capacitor 100 nF X7R 16 V 0402, VDD pin 79/80, joined to the pin before routing (TI SPMA056 3.4.3),Capacitor 100 nF X7R 16 V 0402, VDD pin 90, on the bottom side under the chip (TI SPMA056 3.4.3; Table 7 puts most of the 128-pin package's capacitors on the back),Capacitor 100 nF X7R 16 V 0402, VDDA pin 8 (TI SPMA056 3.4.3),Capacitor 100 nF X7R 16 V 0402, receive-pair termination supply (TI SPMS433B Figure 20-13: 0.1 uF at each pair's resistors),Capacitor 100 nF X7R 16 V 0402, transmit-pair termination supply (TI SPMS433B Figure 20-13),Capacitor 100 nF X7R 16 V 10% 0402, VDDC at pin 115, on the bottom side after C19 (TI SPMA056 3.4.2),Capacitor 100 nF X7R 16 V 10% 0402, VDDC at pin 87, on the bottom side under the chip next to pin 87's via (TI SPMA056 3.4.2, Table 6)","20",""
"C14","10u","Capacitor_SMD:C_0805_2012Metric","Murata","GRM21BR61C106KE15L","Capacitor 10 uF X5R 16 V 0805, VDD/VDDA bulk: 2-22 uF (TI SPMA056 3.4.3)","1",""
"C15,C17,C20,C29,C30,C36,C37,C45","1u","Capacitor_SMD:C_0603_1608Metric","Murata","GCM188R71C105KA64D","Capacitor 1 uF X7R 16 V 0603, CREF at VREFA+ pin 9 to GNDA (TI SPMA056 3.4.5),Capacitor 1 uF X7R 16 V 0603, TPS2116 VIN1, on its pin's side (TI SLVSFG1A section 9),Capacitor 1 uF X7R 16 V 0603, TPS2116 VIN2, on its pin's side (TI SLVSFG1A section 9),Capacitor 1 uF X7R 16 V 0603, TPS22917 input (TI SLVSDW8B section 11: CIN 1 uF),Capacitor 1 uF X7R 16 V 0603, VDDA pin 8 (TI SPMA056 3.4.4),Capacitor 1 uF X7R 16 V 0603, receive centre tap J8.5, on the bottom side beside the pin (TI SPMA056 4.1.2; TI SPMS433B Figure 20-13 note),Capacitor 1 uF X7R 16 V 0603, transmit centre tap J8.2, on the bottom side beside the pin: 1 uF because the switched supply reaches it by a track, not a plane (TI SPMA056 4.1.2; TI SPMS433B Figure 20-13 note),Capacitor 1 uF X7R 16 V 10% 0603, VDDC at pin 115, next after C19 on the bottom side (TI SPMA056 3.4.2)","8",""
"C18,C27","10n","Capacitor_SMD:C_0402_1005Metric","Murata","GRM155R71H103KA88D","Capacitor 10 nF X7R 50 V 0402, CREF at VREFA+ pin 9 to GNDA (TI SPMA056 3.4.5),Capacitor 10 nF X7R 50 V 0402, RST, at the pin, on the bottom side under the chip (TI SPMS433B Figure 5-3; TI SPMA056 3.5.1)","2",""
"C19","2.2u","Capacitor_SMD:C_0603_1608Metric","Murata","GRM188R71A225KE15D","Capacitor 2.2 uF X7R 10 V 10% 0603, VDDC, closest to pin 115: on the bottom side under the chip beside pin 115's via (TI SPMS433B Table 27-15 CLDO 2.5-4.0 uF; TI SPMA056 3.4.2, Table 6)","1",""
"C23,C24","12p","Capacitor_SMD:C_0402_1005Metric","Murata","GRM1555C1H120JA01D","Capacitor 12 pF C0G 50 V 5% 0402, OSC0 load (TI SPMS433B Table 27-24),Capacitor 12 pF C0G 50 V 5% 0402, OSC1 load (TI SPMS433B Table 27-24)","2",""
"C25,C26","20p","Capacitor_SMD:C_0402_1005Metric","Murata","GCM1555C1H200JA16D","Capacitor 20 pF C0G 50 V 5% 0402, XOSC0 load: > 18 pF so OSCDRV = 1, ESR to 75 kohm; CL 12.2-13.0 pF (TI SPMS433B Table 27-22; errata ELEC#04),Capacitor 20 pF C0G 50 V 5% 0402, XOSC1 load (TI SPMS433B Table 27-22)","2",""
"C31","4.7n","Capacitor_SMD:C_1812_4532Metric","KEMET","C1812C472KGRACTU","Capacitor 4.7 nF 2 kV X7R 1812, jack shield to ground (TI SPMS433B Figure 20-13: 4700 pF 2000 V)","1",""
"C32,C34","4.7u","Capacitor_SMD:C_0603_1608Metric","Murata","GRM188R61C475KE11D","Capacitor 4.7 uF X5R 16 V 0603, CP2102N VDD (Silicon Labs CP2102N data sheet Rev. 1.5 Figure 2.3),Capacitor 4.7 uF X5R 16 V 0603, CP2102N VREGIN (Silicon Labs CP2102N data sheet Rev. 1.5 Figure 2.3)","2",""
"C38,C39","22u","Capacitor_SMD:C_1206_3216Metric","Murata","GRM31CR71A226KE15L","Capacitor 22 uF X7R 10 V 1206, 5 V rail (TI SLVSFG1A 7.3.4),Capacitor 22 uF X7R 10 V 1206, TPS2116 VOUT, 5 V rail (TI SLVSFG1A 7.3.2, 7.3.4)","2",""
"C40","4.7u","Capacitor_SMD:C_0805_2012Metric","Murata","GRM21BR71A475KE51L","Capacitor 4.7 uF X7R 10 V 0805, buck input, at VIN (TI SLVSDG1C Table 3, 8.2.2.5)","1",""
"C41","10u","Capacitor_SMD:C_0805_2012Metric","Murata","GRM21BR71A106KA73L","Capacitor 10 uF X7R 10 V 0805, buck output (TI SLVSDG1C Tables 3 and 4: 2.2 uH with 10 uF)","1",""
"C42","6.8p","Capacitor_SMD:C_0402_1005Metric","Murata","GRM1555C1H6R8CA01D","Capacitor 6.8 pF C0G 50 V 0402, feed-forward across R29 (TI SLVSDG1C 8.2.2.2)","1",""
"D1","PN1","LED_SMD:LED_0603_1608Metric","Kingbright","APTD1608LCGCK","LED green 0603, user LED on PN1","1",""
"D2","PN0","LED_SMD:LED_0603_1608Metric","Kingbright","APTD1608LCGCK","LED green 0603, user LED on PN0","1",""
"D3","PF4","LED_SMD:LED_0603_1608Metric","Kingbright","APTD1608LCGCK","LED green 0603, user LED on PF4","1",""
"D4","PF0","LED_SMD:LED_0603_1608Metric","Kingbright","APTD1608LCGCK","LED green 0603, user LED on PF0","1",""
"D5","BAT54J","Diode_SMD:D_SOD-323F","Nexperia","BAT54J","Schottky 30 V, VF <= 240 mV at 0.1 mA (Nexperia BAT54J): VBAT from 3.3 V, a diode drop below VDD","1",""
"D6","PWR","LED_SMD:LED_0603_1608Metric","Kingbright","APTD1608LCGCK","LED green 0603, 3.3 V present (VF 1.9 V typ at 2 mA, DSAO7432)","1",""
"F1,F2","750mA","Fuse:Fuse_1206_3216Metric","Littelfuse","1206L075THYR","PTC fuse 0.75 A hold (0.65 A at 40 C), 1.50 A trip, 8 V, R1max 0.29 ohm, 1206, debug port (Littelfuse 1206L, revised 10/29/21),PTC fuse 0.75 A hold (0.65 A at 40 C), 1.50 A trip, 8 V, R1max 0.29 ohm, 1206, device port (Littelfuse 1206L, revised 10/29/21)","2",""
"J1","BoosterPack 1 A/B","Connector_PinHeader_2.54mm:PinHeader_2x10_P2.54mm_Vertical","Samtec","SSW-110-23-F-D","BoosterPack 1 rows A (odd pins, outer) and B (even pins, inner), 2x10 2.54 mm, female, long male leads, as TI's BoosterPack Pinout Standard (Sept 1, 2013) p. 2 asks and recommends","1",""
"J2","BoosterPack 1 C/D","Connector_PinHeader_2.54mm:PinHeader_2x10_P2.54mm_Vertical","Samtec","SSW-110-23-F-D","BoosterPack 1 rows C (odd pins, inner) and D (even pins, outer), 2x10 2.54 mm, female, long male leads, as TI's BoosterPack Pinout Standard (Sept 1, 2013) p. 2 asks and recommends","1",""
"J3","BoosterPack 2 A/B","Connector_PinHeader_2.54mm:PinHeader_2x10_P2.54mm_Vertical","Samtec","SSW-110-23-F-D","BoosterPack 2 rows A (odd pins, outer) and B (even pins, inner), 2x10 2.54 mm, female, long male leads, as TI's BoosterPack Pinout Standard (Sept 1, 2013) p. 2 asks and recommends","1",""
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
